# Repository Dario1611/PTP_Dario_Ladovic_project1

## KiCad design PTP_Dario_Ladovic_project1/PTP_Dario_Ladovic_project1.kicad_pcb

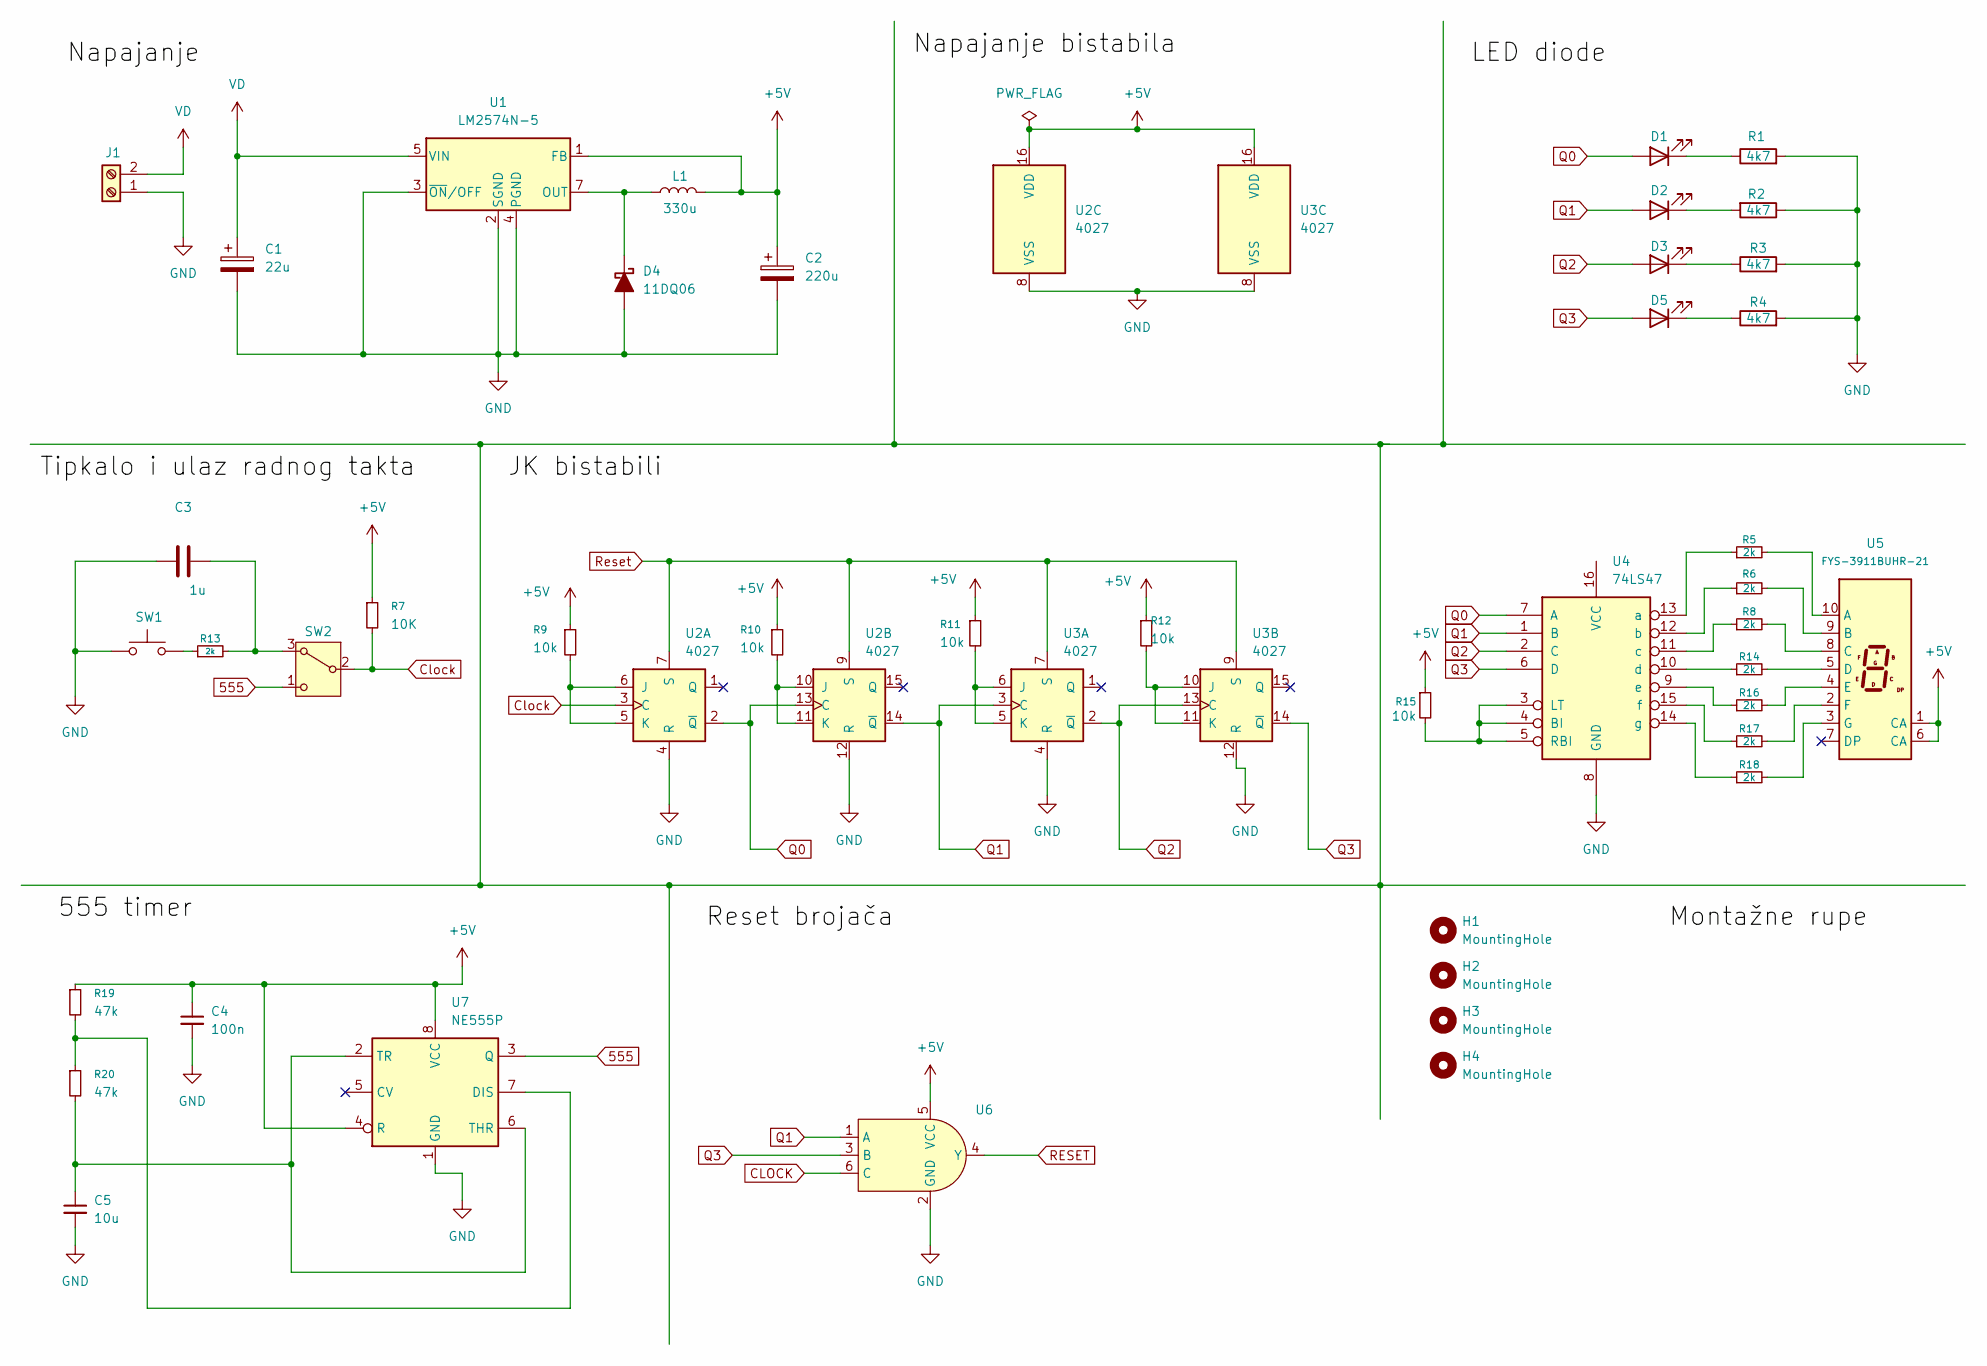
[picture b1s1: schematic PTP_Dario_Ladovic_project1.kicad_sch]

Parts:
C1: 22u; CP_Radial_D5.0mm_P2.00mm; Manufacturer Part Number EWH1EM220D11OT
C2: 220u; CP_Radial_D5.0mm_P2.00mm; Manufacturer Part Number RD1A227M05011BB
C3: 1u; C_1206_3216Metric_Pad1.33x1.80mm_HandSolder
C4: 100n; C_1206_3216Metric_Pad1.33x1.80mm_HandSolder
C5: 10u; C_1206_3216Metric_Pad1.33x1.80mm_HandSolder
D1: LED_D5.0mm
D2, D3, D5: LED; LED_D5.0mm
D4: 11DQ06; D_DO-41_SOD81_P12.70mm_Horizontal
H1, H2, H3, H4: MountingHole; MountingHole_5.5mm
J1: TerminalBlock_MetzConnect_Type011_RT05502HBLC_1x02_P5.00mm_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
L1: 330u; L_Radial_D7.2mm_P3.00mm_Murata_1700
R1, R2, R3, R4: 4k7; R_Axial_DIN0207_L6.3mm_D2.5mm_P10.16mm_Horizontal
R5, R6, R8, R13, R14, R16, R17, R18: 2k; R_1206_3216Metric_Pad1.30x1.75mm_HandSolder
R7: 10K; R_1206_3216Metric_Pad1.30x1.75mm_HandSolder
R9, R10, R11, R12, R15: 10k; R_1206_3216Metric_Pad1.30x1.75mm_HandSolder
R19, R20: 47k; R_1206_3216Metric_Pad1.30x1.75mm_HandSolder
SW1: SW_PUSH_6mm_H4.3mm
SW2: SW_Slide_SPDT_Straight_CK_OS102011MS2Q
U1: LM2574N-5; DIP-8_W7.62mm
U2, U3: 4027; DIP-16_W7.62mm_Socket_LongPads
U4: 74LS47; DIP-16_W7.62mm_Socket_LongPads
U5: FYS-3911BUHR-21; HDSP-7401
U6: SOT-23-6
U7: NE555P; DIP-8_W7.62mm

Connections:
555: SW2.1 (C), U7.3 (Q)
+5V: C2.1, C4.1, L1.2, R7.1, R9.1, R10.1, R11.1, R12.1, R15.1, R19.1, U1.1 (FB), U2.16 (VDD), U3.16 (VDD), U5.1 (CA), U5.6 (CA), U6.5 (VCC), U7.4 (R), U7.8 (VCC)
CLOCK: U6.6 (C)
Clock: R7.2, SW2.2 (B), U2.3 (C)
GND: C1.2, C2.2, C3.1, C4.2, C5.2, D4.2 (A), J1.1, R1.2, R2.1, R3.2, R4.2, SW1.1 (A), SW1.2 (A), U1.2 (SGND), U1.3 (~ON/OFF), U1.4 (PGND), U2.4 (R), U2.8 (VSS), U2.12 (R), U3.4 (R), U3.8 (VSS), U3.12 (R), U4.8 (GND), U6.2 (GND), U7.1 (GND)
unnamed: D1.1 (K), R1.1
unnamed: D2.1 (K), R2.2
unnamed: D3.1 (K), R3.1
unnamed: D4.1 (K), L1.1, U1.7 (OUT)
unnamed: D5.1 (K), R4.1
unnamed: R13.1, SW1.3 (B), SW1.4 (B)
unnamed: C3.2, R13.2, SW2.3 (A)
unnamed: R9.2, U2.5 (K), U2.6 (J)
unnamed: R10.2, U2.10 (J), U2.11 (K)
unnamed: R11.2, U3.5 (K), U3.6 (J)
unnamed: R12.2, U3.10 (J), U3.11 (K)
unnamed: R15.2, U4.3 (LT), U4.4 (BI), U4.5 (RBI)
unnamed: R5.1, U4.13 (a)
unnamed: R6.1, U4.12 (b)
unnamed: R8.1, U4.11 (c)
unnamed: R14.1, U4.10 (d)
unnamed: R16.1, U4.9 (e)
unnamed: R17.1, U4.15 (f)
unnamed: R18.1, U4.14 (g)
unnamed: R5.2, U5.10 (A)
unnamed: R6.2, U5.9 (B)
unnamed: R8.2, U5.8 (C)
unnamed: R14.2, U5.5 (D)
unnamed: R16.2, U5.4 (E)
unnamed: R17.2, U5.2 (F)
unnamed: R18.2, U5.3 (G)
unnamed: R19.2, R20.1, U7.7 (DIS)
unnamed: C5.1, R20.2, U7.2 (TR), U7.6 (THR)
Q0: D1.2 (A), U2.2 (~Q), U2.13 (C), U4.7 (A)
Q1: D2.2 (A), U2.14 (~Q), U3.3 (C), U4.1 (B), U6.1 (A)
Q2: D3.2 (A), U3.2 (~Q), U3.13 (C), U4.2 (C)
Q3: D5.2 (A), U3.14 (~Q), U4.6 (D), U6.3 (B)
RESET: U6.4 (Y)
Reset: U2.7 (S), U2.9 (S), U3.7 (S), U3.9 (S)
VD: C1.1, J1.2, U1.5 (VIN)

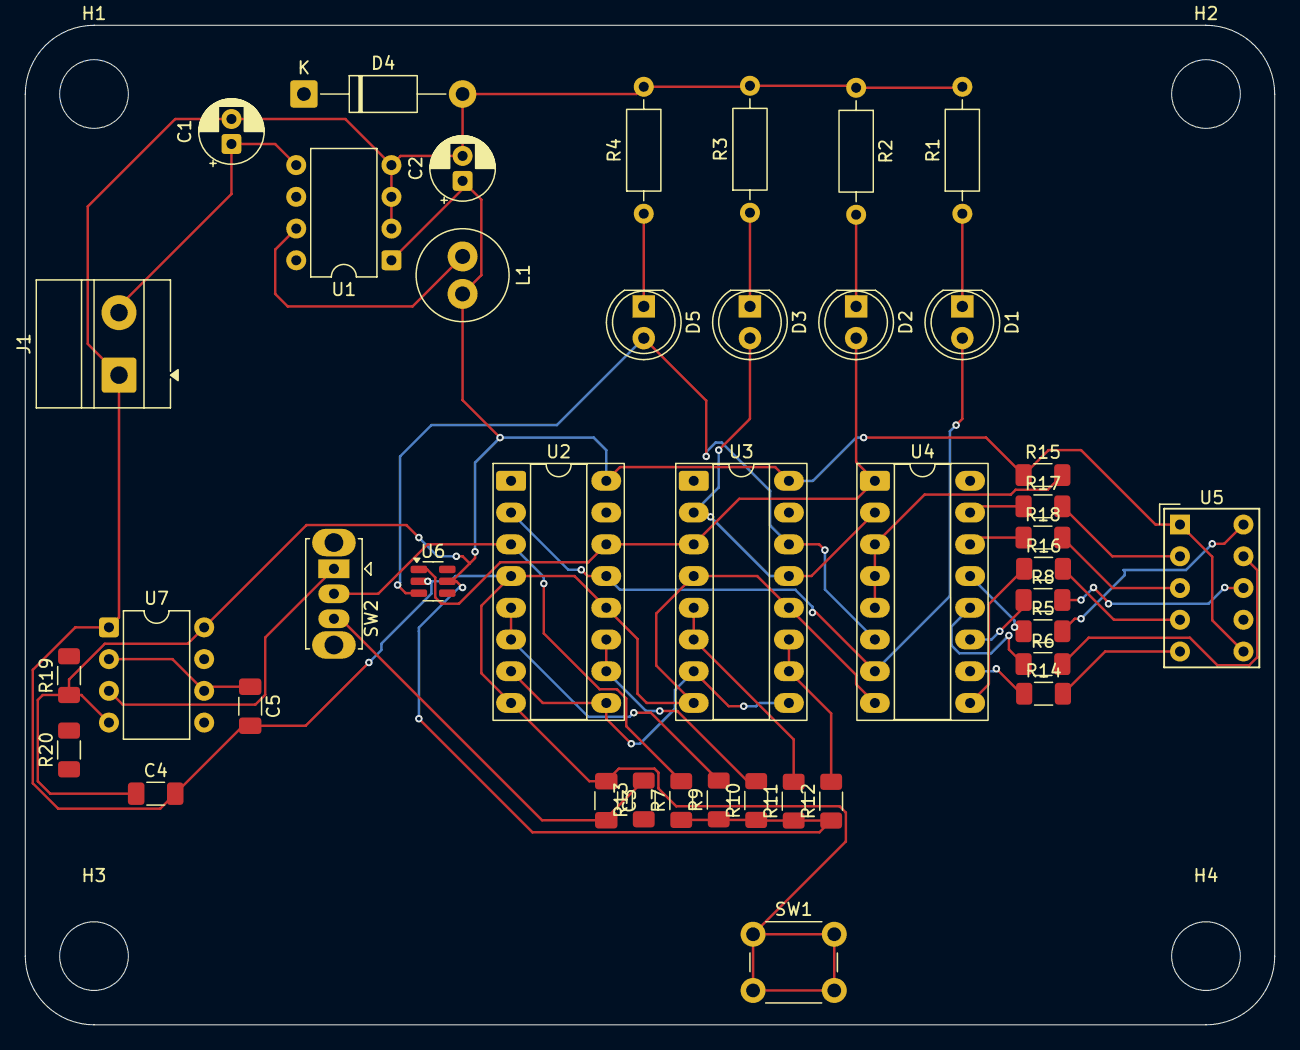
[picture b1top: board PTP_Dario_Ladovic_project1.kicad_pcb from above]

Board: 2 copper layers, 100.0 x 80.0 mm, 45 parts (0 on the bottom side), 37 nets.

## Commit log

2025-10-28 Dodali smo NE555
2025-11-11 Vjezba 6. tjedan
2025-11-11 Promjena grešaka
2025-12-09 Slaganje plocice za spajanje komponenata
2025-12-16 Dokumentiranje
